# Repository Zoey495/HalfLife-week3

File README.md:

# HalfLife-week3
Week three following of HalfLife's guides.

In this project, I was told to make the hardware and PCB for a midi keypad or something similar. I chose to focus more on the capacitive touch buttons. I used kicad to create the PCB design and to plan how the project will look once build.

This is the schematic diagram -->

A schematic diagram is a diagram showing how all the components are connected. Using kicad, you assign footprints/real components to every symbol and device. This allows kicad to translate the schematic diagram into a PCB. 

Using kicad, I created a PCB -->

A PCB is in simple words, a circuit board that connects all the components using conductive wires embedded inside of it within layers. In this case, the red lines represent the connections in the top of the board, while the blue wires represent the connections in the back of the board. The pale yellow is simply words/images that are to be printed on the board. The large red images are custom made footprints meant to act as the capacitive touch buttons in the physical PCB.

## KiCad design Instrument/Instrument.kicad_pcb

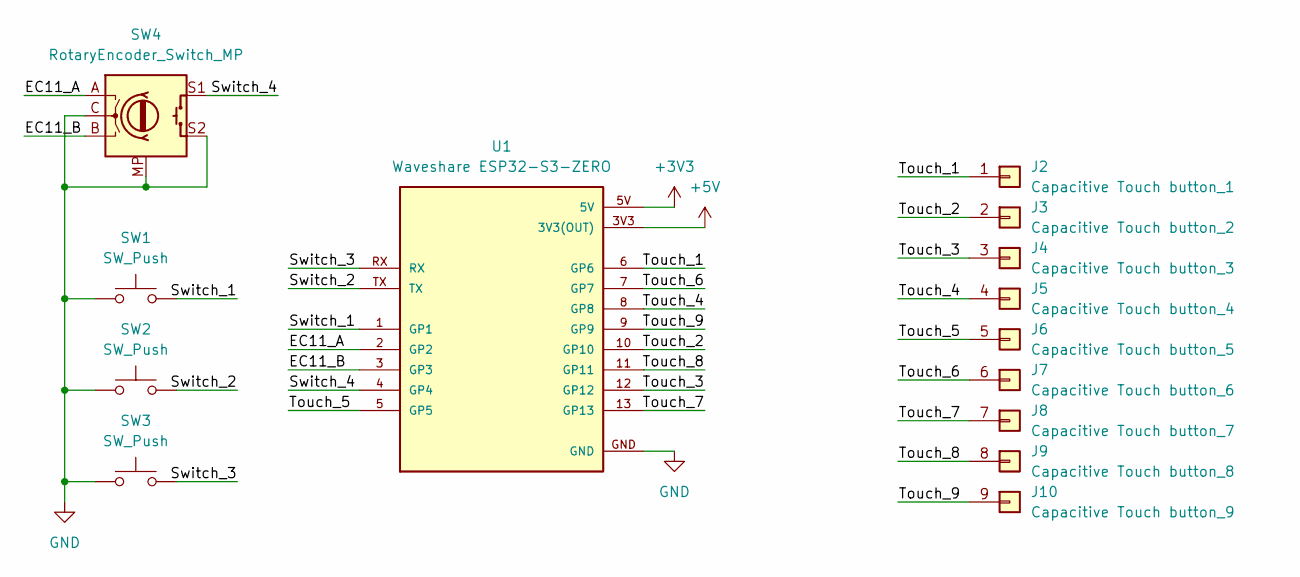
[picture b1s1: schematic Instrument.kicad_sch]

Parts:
J2: Capacitive Touch button_1; Butterfly_1
J3: Capacitive Touch button_2; Butterfly_2
J4: Capacitive Touch button_3; Butterfly_3
J5: Capacitive Touch button_4; Butterfly_4
J6: Capacitive Touch button_5; Flower_5
J7: Capacitive Touch button_6; Flower_6
J8: Capacitive Touch button_7; Flower_7
J9: Capacitive Touch button_8; Flower_8
J10: Capacitive Touch button_9; CenterPiece_9
SW1, SW2, SW3: SW_Push; Kailh Choc Low-Profile Switches
SW4: RotaryEncoder_Switch_MP; RotaryEncoder_Alps_EC11E-Switch_Vertical_H20mm
U1: Waveshare ESP32-S3-ZERO; Waveshare ESP32-S3-Zero; PARTREV NA

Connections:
+3V3: U1.5V
+5V: U1.3V3 (3V3(OUT))
/EC11_A: SW4.A, U1.2 (GP2)
/EC11_B: SW4.B, U1.3 (GP3)
/Switch_1: SW1.2, U1.1 (GP1)
/Switch_2: SW2.2, U1.TX
/Switch_3: SW3.2, U1.RX
/Switch_4: SW4.S1, U1.4 (GP4)
/Touch_1: J2.1 (Pin_1_1), U1.6 (GP6)
/Touch_2: J3.2 (Pin_1_2), U1.10 (GP10)
/Touch_3: J4.3 (Pin_1_3), U1.12 (GP12)
/Touch_4: J5.4 (Pin_1_4), U1.8 (GP8)
/Touch_5: J6.5 (Pin_1_5), U1.5 (GP5)
/Touch_6: J7.6 (Pin_1_6), U1.7 (GP7)
/Touch_7: J8.7 (Pin_1_7), U1.13 (GP13)
/Touch_8: J9.8 (Pin_1_8), U1.11 (GP11)
/Touch_9: J10.9 (Pin_1_9), U1.9 (GP9)
GND: SW1.1, SW2.1, SW3.1, SW4.C, SW4.MP, SW4.S2, U1.GND

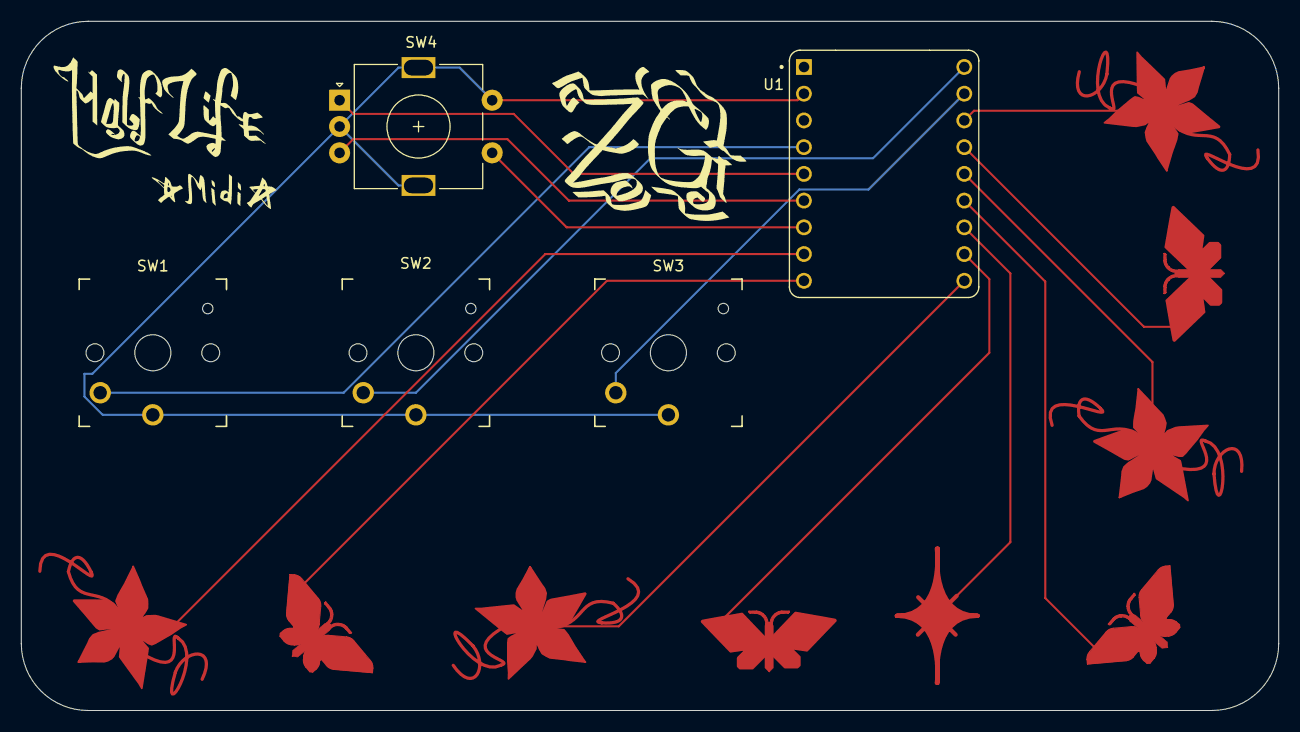
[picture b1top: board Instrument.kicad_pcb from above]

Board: 2 copper layers, 119.5 x 65.5 mm, 14 parts (0 on the bottom side), 16 nets.
